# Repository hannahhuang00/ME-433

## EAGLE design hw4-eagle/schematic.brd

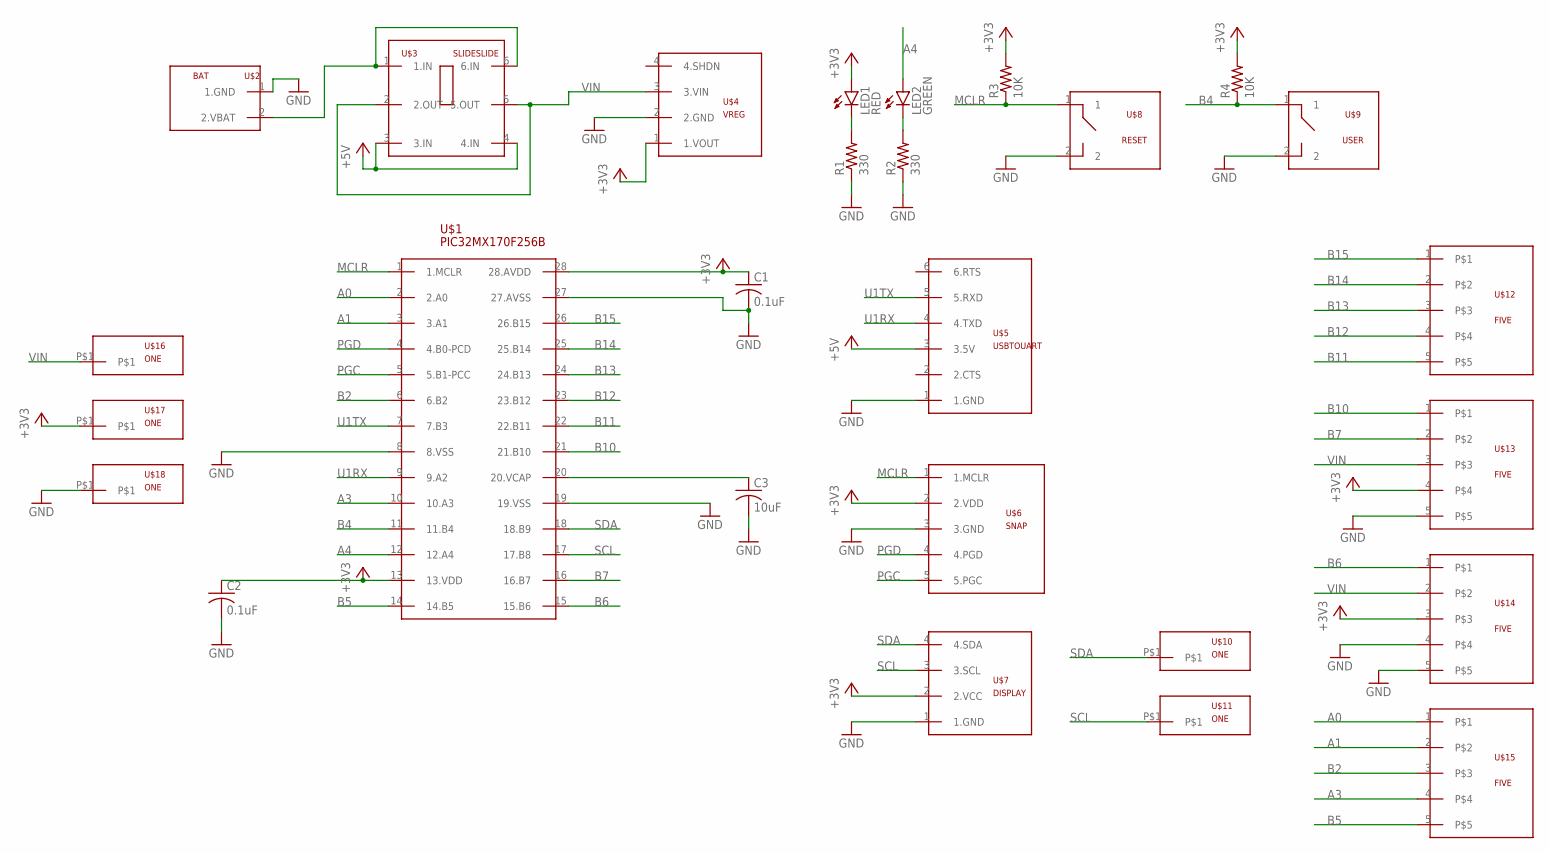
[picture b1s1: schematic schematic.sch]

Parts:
C1, C2: 0.1uF; C025-024X044
C3: 10uF; C025-024X044
LED1: RED; LED3MM
LED2: GREEN; LED3MM
R1, R2: 330; 0207/7
R3, R4: 10K; 0207/7
U$1: PIC32MX170F256B; DIL28-3
U$2: BAT
U$3: SLIDESLIDE; SLIDE
U$4: VREG
U$5: USBTOUART
U$6: SNAP
U$7: DISPLAY
U$8: RESET; BUTTON
U$9: USER; BUTTON
U$10, U$11, U$16, U$17, U$18: ONE
U$12, U$13, U$14, U$15: FIVE

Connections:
+5V: U$3.3 (3.IN), U$3.4 (4.IN), U$5.3 (3.5V)
A0: U$1.2 (2.A0), U$15.1
A1: U$1.3 (3.A1), U$15.2
A3: U$1.10 (10.A3), U$15.4
A4: LED2.A, U$1.12 (12.A4)
B2: U$1.6 (6.B2), U$15.3
B4: R4.1, U$1.11 (11.B4), U$9.1
B5: U$1.14 (14.B5), U$15.5
B6: U$1.15 (15.B6), U$14.1
B7: U$1.16 (16.B7), U$13.2
B10: U$1.21 (21.B10), U$13.1
B11: U$1.22 (22.B11), U$12.5
B12: U$1.23 (23.B12), U$12.4
B13: U$1.24 (24.B13), U$12.3
B14: U$1.25 (25.B14), U$12.2
B15: U$1.26 (26.B15), U$12.1
GND: C1.2, C2.2, C3.2, R1.1, R2.1, U$1.8 (8.VSS), U$1.19 (19.VSS), U$1.27 (27.AVSS), U$2.1 (1.GND), U$4.2 (2.GND), U$5.1 (1.GND), U$6.3 (3.GND), U$7.1 (1.GND), U$8.2, U$9.2, U$13.5, U$14.4, U$14.5, U$18.P$1
MCLR: R3.1, U$1.1 (1.MCLR), U$6.1 (1.MCLR), U$8.1
unnamed: U$2.2 (2.VBAT), U$3.1 (1.IN), U$3.6 (6.IN)
unnamed: LED1.K (C), R1.2
unnamed: C3.1, U$1.20 (20.VCAP)
unnamed: LED2.K (C), R2.2
PGC: U$1.5 (5.B1-PCC), U$6.5 (5.PGC)
PGD: U$1.4 (4.B0-PCD), U$6.4 (4.PGD)
SCL: U$1.17 (17.B8), U$7.3 (3.SCL), U$11.P$1
SDA: U$1.18 (18.B9), U$7.4 (4.SDA), U$10.P$1
U1RX: U$1.9 (9.A2), U$5.4 (4.TXD)
U1TX: U$1.7 (7.B3), U$5.5 (5.RXD)
VIN: U$3.2 (2.OUT), U$3.5 (5.OUT), U$4.3 (3.VIN), U$13.3, U$14.2, U$16.P$1

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
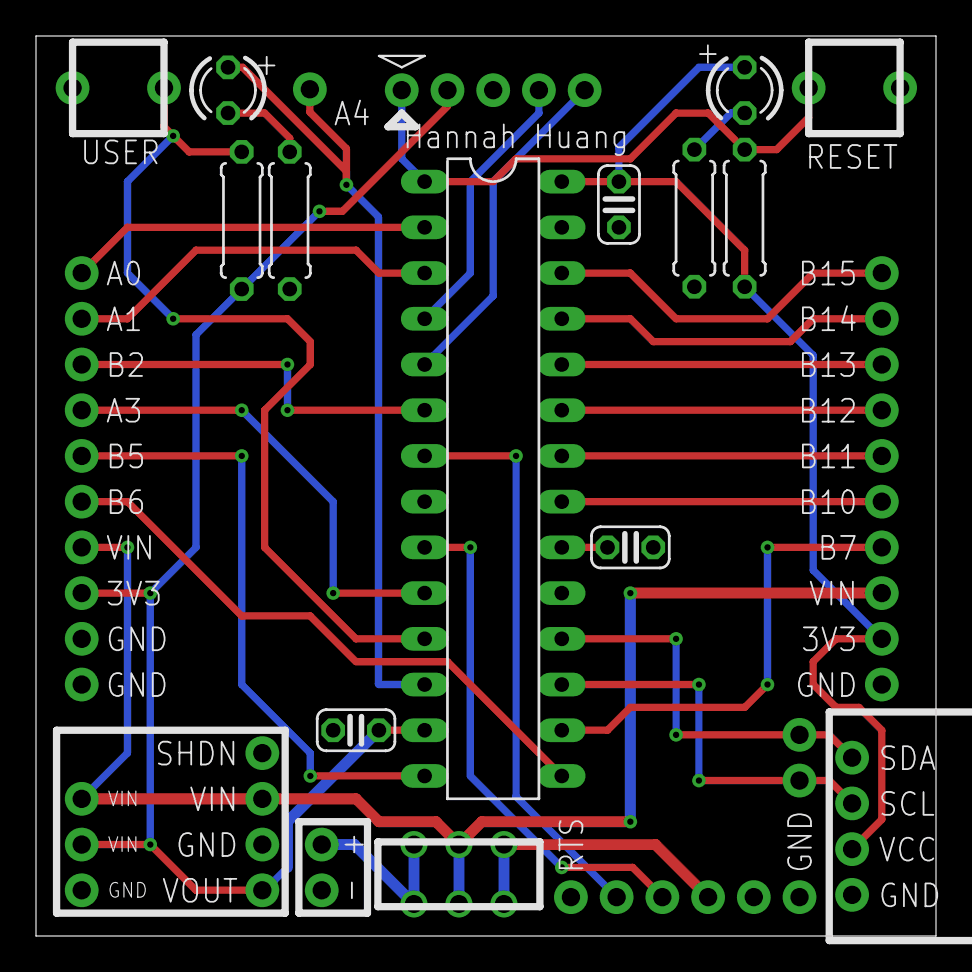
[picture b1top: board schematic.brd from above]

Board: 2 copper layers, 50.0 x 50.0 mm, 27 parts (0 on the bottom side), 31 nets.

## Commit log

2022-04-04 add hw2
2022-04-04 added pictures and video
2022-04-04 nscope
2022-04-04 restructure
2022-04-06 hw 3
2022-04-18 HW 4 added
2022-04-19 added hw 5
2022-04-24 hw 6
2022-05-05 hw 8
2022-05-05 hw 8 new video
2022-05-06 hw 9
2022-05-20 hw 10
2022-05-22 hw11
